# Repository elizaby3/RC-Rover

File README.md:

## Main Purpose
The goal of this project is to make a remote controlled rover from scratch. I am currently working on getting the PCB manufactured and wiring and soldering different components together.

## Current Progress
### Schematic and PCB Design

First I started out with making the schematic where the ESP32 board in the middle connects to a connection scoket for the joystick controller and two LEDs and resistors that I will eventually program to indicate when the remote controller is on or off.

After I had finished my schematic, I routed the PCB on Kicad and used a ground fill to connect the grounds as shown above.

[Link to Main Projects Page](https://elizaby3.github.io)

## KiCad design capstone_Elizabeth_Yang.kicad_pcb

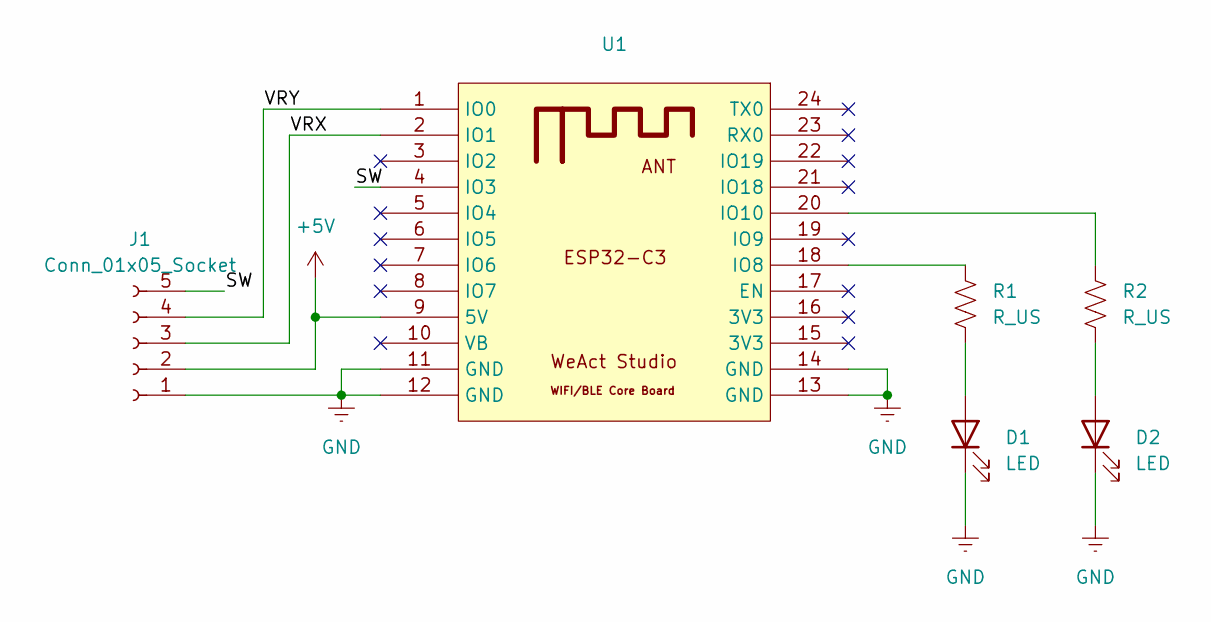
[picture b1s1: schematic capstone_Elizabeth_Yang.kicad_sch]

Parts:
D1, D2: LED; LED_D3.0mm
J1: Conn_01x05_Socket; PinSocket_1x05_P2.54mm_Vertical
R1, R2: R_US; R_Axial_DIN0207_L6.3mm_D2.5mm_P7.62mm_Horizontal
U1: WeAct-ESP32-C3Fx4-CoreBoard

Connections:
+5V: J1.2, U1.9 (5V)
/SW: J1.5, U1.4 (IO3)
/VRX: J1.3, U1.2 (IO1)
/VRY: J1.4, U1.1 (IO0)
GND: D1.1 (K), D2.1 (K), J1.1, U1.11 (GND), U1.12 (GND), U1.13 (GND), U1.14 (GND)
unnamed: D1.2 (A), R1.2
unnamed: D2.2 (A), R2.2
unnamed: R1.1, U1.18 (IO8)
unnamed: R2.1, U1.20 (IO10)

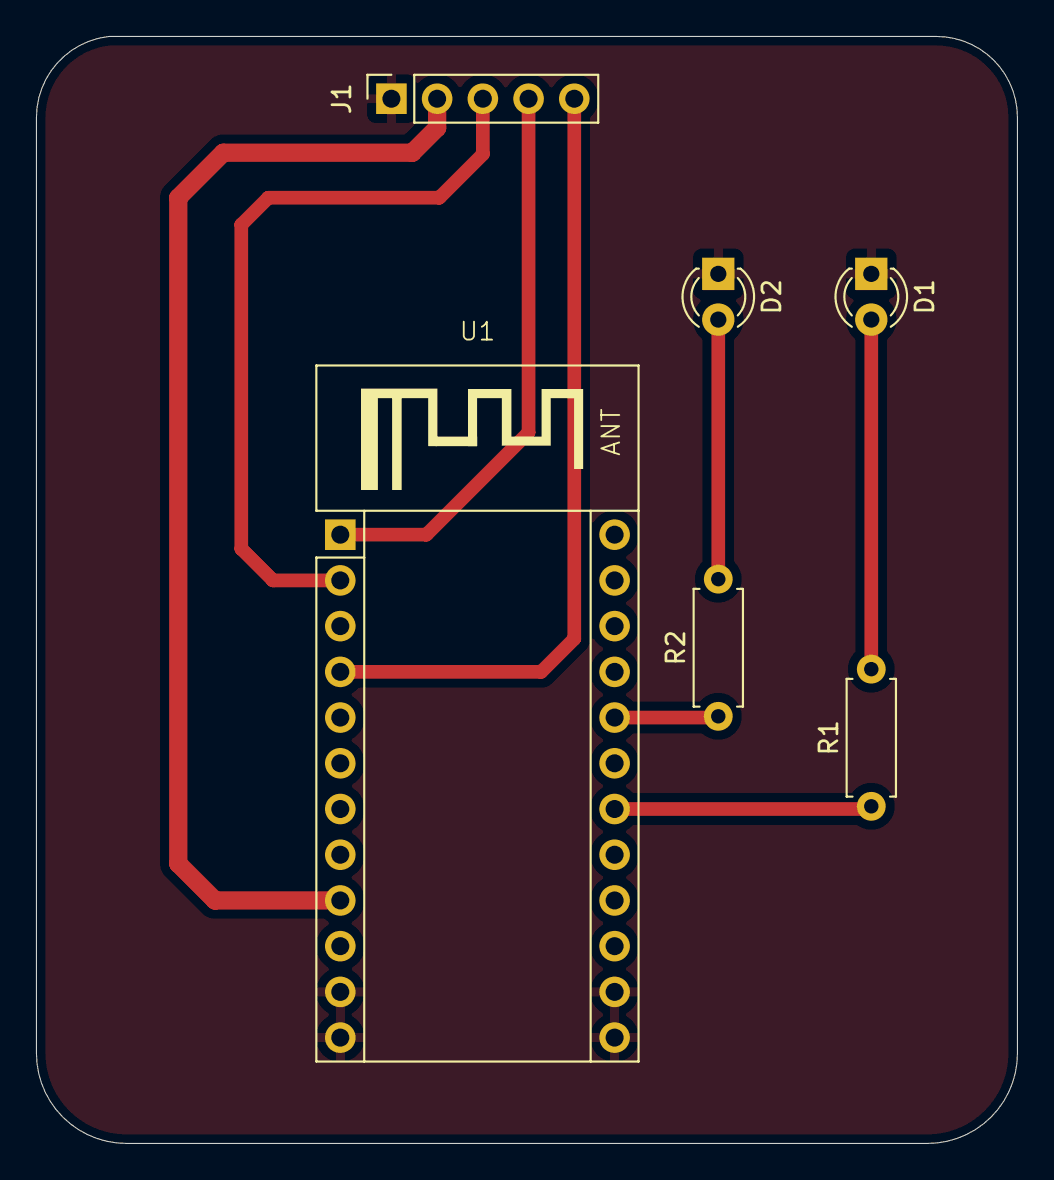
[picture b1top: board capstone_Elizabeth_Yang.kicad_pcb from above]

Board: 2 copper layers, 54.5 x 61.5 mm, 6 parts (0 on the bottom side), 9 nets.

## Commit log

2025-04-11 Kicad Files
2025-04-11 Organization
2025-04-11 Rename Screenshot 2025-04-11 021014.png to photos/pcb.png
2025-04-11 extra image deletion
2025-04-11 Rename Screenshot 2025-04-11 020706.png to schematic.png
